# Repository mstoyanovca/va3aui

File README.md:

Direct RF sampling HF SDR transceiver

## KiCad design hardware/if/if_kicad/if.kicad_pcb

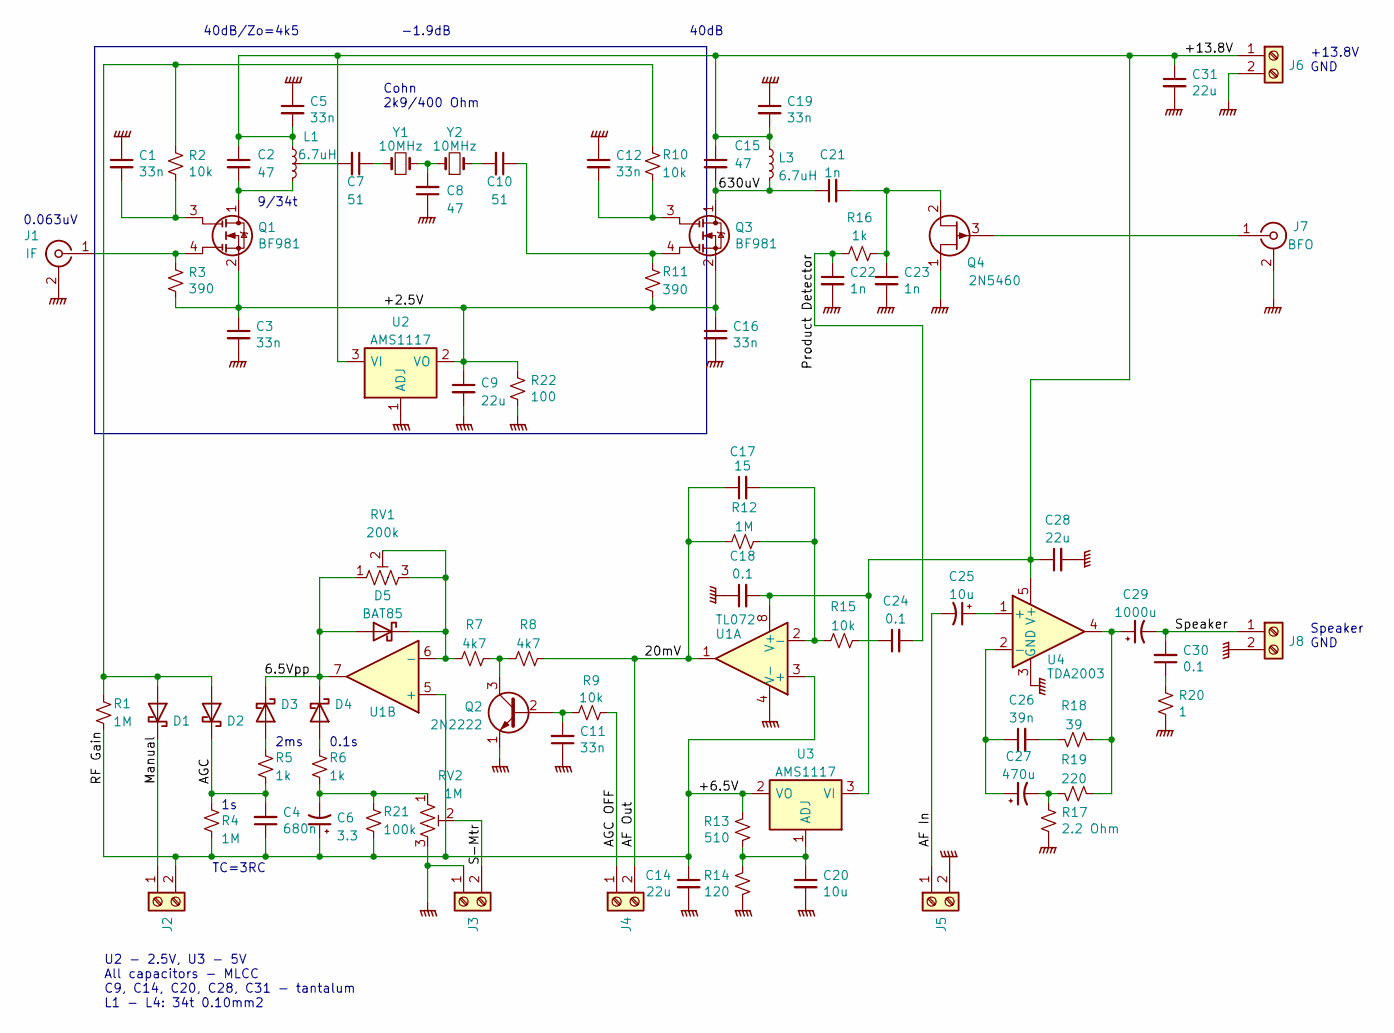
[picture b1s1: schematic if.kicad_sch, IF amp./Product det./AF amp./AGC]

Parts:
C1, C3, C5, C11, C12, C16, C19: 33n; C_Disc_D5.1mm_W3.2mm_P5.00mm_MLCC
C2, C8, C15: 47; C_Disc_D5.1mm_W3.2mm_P5.00mm_MLCC
C4: 680n; C_Disc_D5.1mm_W3.2mm_P5.00mm_MLCC
C6: 3.3; CP_Radial_D4.0mm_H5.0mm_P1.50mm
C7, C10: 51; C_Disc_D5.1mm_W3.2mm_P5.00mm_MLCC
C9, C14, C28, C31: 22u; CP_Radial_Tantal_D5.5mm_P5.00mm
C17: 15; C_Disc_D5.1mm_W3.2mm_P5.00mm_MLCC
C18, C24, C30: 0.1; C_Disc_D5.1mm_W3.2mm_P5.00mm_MLCC
C20: 10u; C_Disc_D5.1mm_W3.2mm_P5.00mm_MLCC
C21, C22, C23: 1n; C_Disc_D5.1mm_W3.2mm_P5.00mm_MLCC
C25: 10u; CP_Radial_D4.0mm_H5.0mm_P2.50mm
C26: 39n; C_Disc_D5.1mm_W3.2mm_P5.00mm_MLCC
C27: 470u; CP_Radial_D6.3mm_H5.0mm_P2.50mm
C29: 1000u; CP_Radial_D8.0mm_H11.5mm_P3.50mm
D1, D2, D3, D4, D5: BAT85; D_DO-35_SOD27_P7.62mm_Horizontal
J1: IF; SMA
J2, J3, J4, J5, J6, J8: Screw_Terminal_01x02; 2poles_screw_tb
J7: BFO; SMA
L1: 6.7uH; Filter_IF_tap
L3: 6.7uH; Filter_IF
Q1, Q3: BF981
Q2: 2N2222; TO-92_2N2222
Q4: 2N5460; TO-92_2N5460
R1, R4, R12: 1M; R_Axial_DIN0207_L6.3mm_D2.5mm_P10.16mm_Horizontal
R2, R9, R10, R15: 10k; R_Axial_DIN0207_L6.3mm_D2.5mm_P10.16mm_Horizontal
R3, R11: 390; R_Axial_DIN0207_L6.3mm_D2.5mm_P10.16mm_Horizontal
R5, R6, R16: 1k; R_Axial_DIN0207_L6.3mm_D2.5mm_P10.16mm_Horizontal
R7, R8: 4k7; R_Axial_DIN0207_L6.3mm_D2.5mm_P10.16mm_Horizontal
R13: 510; R_Axial_DIN0207_L6.3mm_D2.5mm_P10.16mm_Horizontal
R14: 120; R_Axial_DIN0207_L6.3mm_D2.5mm_P10.16mm_Horizontal
R17: 2.2 Ohm; R_Axial_DIN0207_L6.3mm_D2.5mm_P10.16mm_Horizontal
R18: 39; R_Axial_DIN0207_L6.3mm_D2.5mm_P10.16mm_Horizontal
R19: 220; R_Axial_DIN0207_L6.3mm_D2.5mm_P10.16mm_Horizontal
R20: 1; R_Axial_DIN0207_L6.3mm_D2.5mm_P10.16mm_Horizontal
R21: 100k; R_Axial_DIN0207_L6.3mm_D2.5mm_P10.16mm_Horizontal
R22: 100; R_Axial_DIN0207_L6.3mm_D2.5mm_P10.16mm_Horizontal
RV1: 200k; R_trimmer
RV2: 1M; R_trimmer
U1: TL072
U2, U3: AMS1117
U4: TDA2003; TDA2203
Y1, Y2: 10MHz; HC49-U

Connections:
/6.5Vpp: D3.1 (K), D4.1 (K), D5.2 (A), RV1.1, U1.7
/20mV: C17.1, J4.2, R8.2, R12.1, U1.1
/630uV: C15.2, C21.1, L3.2, L3.5, Q3.1 (D)
/+2.5V: C3.1, C9.1, C16.1, Q1.2 (S), Q3.2 (S), R3.2, R11.2, R22.1, U2.2 (VO); also elsewhere on the board
/+6.5V: C4.1, C6.1, C14.1, J2.2, R1.2, R4.2, R13.1, R21.2, U1.3 (+), U1.5 (+), U3.2 (VO)
/+13.8V: C2.1, C5.2, C15.1, C18.2, C19.2, C28.1, C31.1, J6.1, L1.1, L3.1, L3.3, U1.8 (V+), U2.3 (VI), U3.3 (VI), U4.5 (V+)
/AF In: C25.2, J5.1
/AGC: C4.2, D2.1 (K), R4.1, R5.2
/AGC OFF: J4.1, R9.2
/Manual: D1.1 (K), J2.1
/Product Detector: C22.1, C24.2, R16.1
/Speaker: C29.2, C30.2, J8.1
GNDPWR: C1.1, C3.2, C5.1, C8.1, C9.2, C11.1, C12.1, C14.2, C16.2, C18.1, C19.1, C20.2, C22.2, C23.2, C28.2, C31.2, J1.2 (Ext), J3.1, J5.2, J6.2, J7.2 (Ext), J8.2, L1.6, L1.7, L3.6, L3.7, Q2.1 (E), Q4.1 (S), R14.2, R17.2, R20.2, R22.2, RV2.3, U1.4 (V-), U2.1 (ADJ), U4.3 (GND); also elsewhere on the board
unnamed: C1.2, Q1.3 (G1), R2.2
unnamed: C2.2, L1.2, Q1.1 (D)
unnamed: C6.2, R6.2, R21.1, RV2.1
unnamed: C7.1, Y1.1
unnamed: C7.2, L1.3
unnamed: C8.2, Y1.2, Y2.1
unnamed: C10.2, Y2.2
unnamed: C11.2, Q2.2 (B), R9.1
unnamed: C12.2, Q3.3 (G1), R10.2
unnamed: C17.2, R12.2, R15.1, U1.2 (-)
unnamed: C20.1, R13.2, R14.1, U3.1 (ADJ)
unnamed: C21.2, C23.1, Q4.2 (D), R16.2
unnamed: C24.1, R15.2
unnamed: C25.1, U4.1 (+)
unnamed: C26.1, C27.1, U4.2 (-)
unnamed: C26.2, R18.2
unnamed: C27.2, R17.1, R19.2
unnamed: C29.1, R18.1, R19.1, U4.4
unnamed: C30.1, R20.1
unnamed: D1.2 (A), D2.2 (A), R1.1, R2.1, R10.1
unnamed: D3.2 (A), R5.1
unnamed: D4.2 (A), R6.1
unnamed: D5.1 (K), R7.1, RV1.2, RV1.3, U1.6 (-)
unnamed: J1.1 (In), Q1.4 (G2), R3.1
unnamed: J3.2, RV2.2
unnamed: J7.1 (In), Q4.3 (G)
unnamed: Q2.3 (C), R7.2, R8.1

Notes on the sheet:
TC=3RC
Cohn 2k9/400 Ohm
Speaker GND
0.063uV
40dB/Zo=4k5
0.1s
U2 - 2.5V, U3 - 5V All capacitors - MLCC C9, C14, C20, C28, C31 - tantalum L1 - L4: 34t 0.10mm2
2ms
9/34t
-1.9dB
40dB
+13.8V GND

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
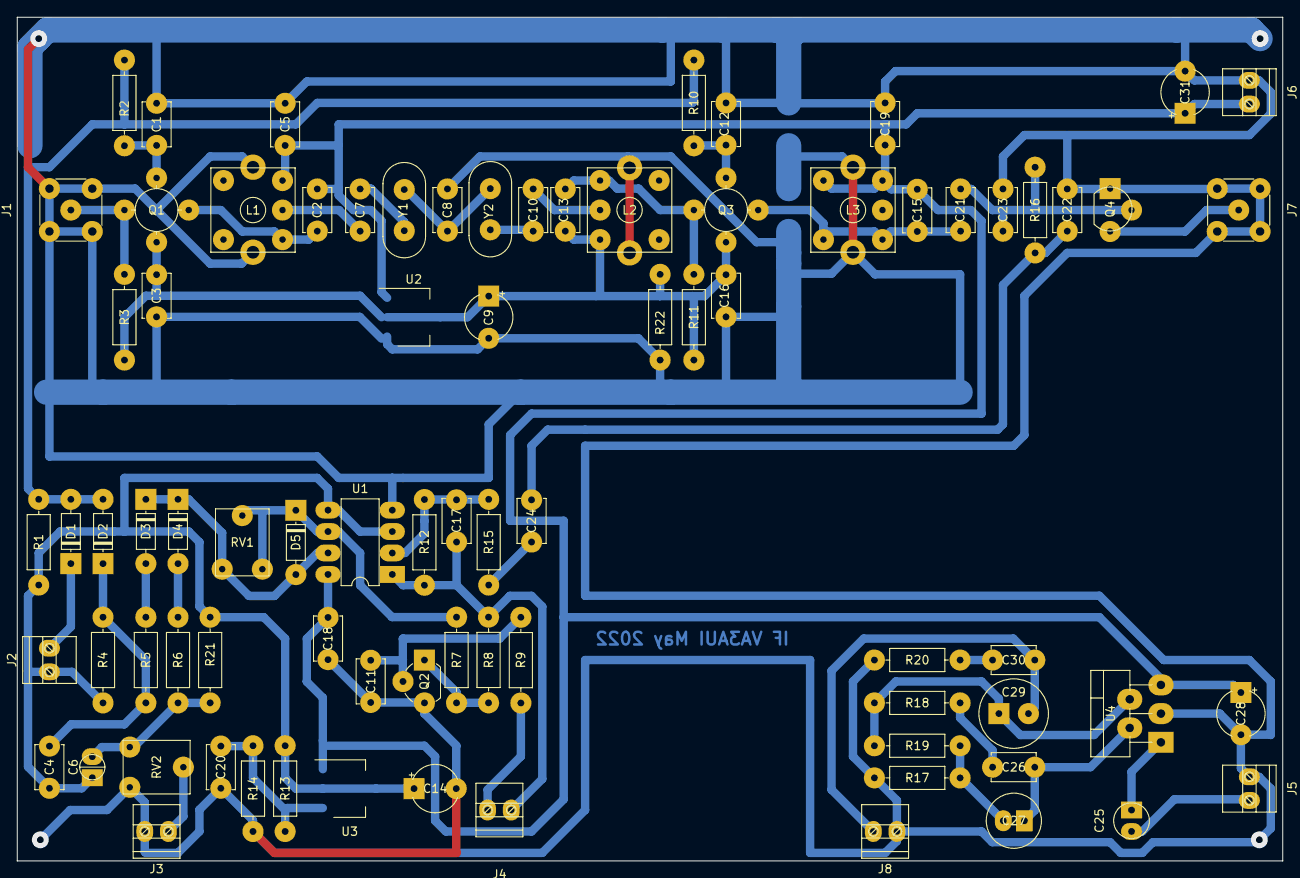
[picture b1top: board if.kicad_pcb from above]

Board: 2 copper layers, 150.0 x 100.0 mm, 81 parts (0 on the bottom side), 42 nets.

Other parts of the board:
C13: 47; C_Disc_D5.1mm_W3.2mm_P5.00mm_MLCC
L2: 6.7uH; Filter_IF_tap

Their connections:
/+2.5V: C13.2, L2.1; also elsewhere on the board
GNDPWR: L2.6, L2.7; also elsewhere on the board

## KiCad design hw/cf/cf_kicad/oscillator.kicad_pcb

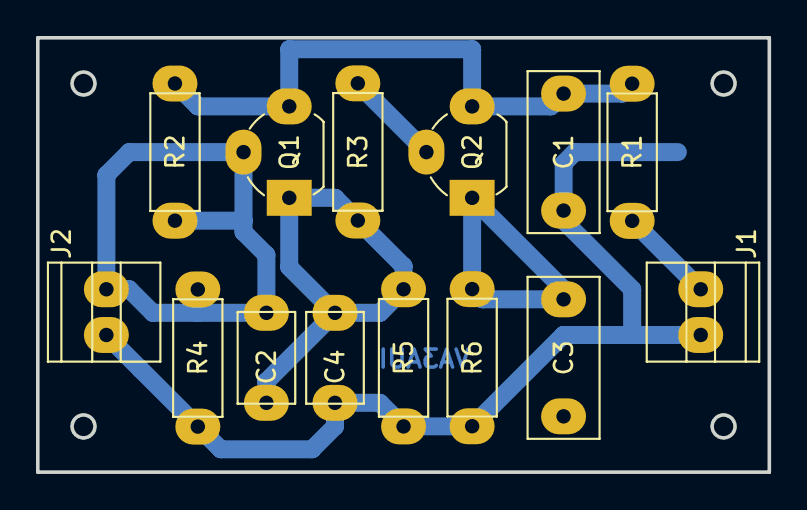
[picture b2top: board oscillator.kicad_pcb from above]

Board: 2 copper layers, 40.6 x 24.1 mm, 14 parts (0 on the bottom side), 7 nets.

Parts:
C1, C3: 0.1; C_Disc_D9.0mm_W4.0mm_P6.50mm_100n
C2: 150; C_Disc_D5.1mm_W3.2mm_P5.00mm_MLCC
C4: 330; C_Disc_D5.1mm_W3.2mm_P5.00mm_MLCC
J1: +13.8V; 2poles_screw_tb
J2: Crystal 3MHz; 2poles_screw_tb
Q1, Q2: 2N3904; TO-92_2N3904
R1: 47; R_Axial_L6.3mm_D2.5mm_P7.62mm_0.25W
R2, R4: 10k; R_Axial_L6.3mm_D2.5mm_P7.62mm_0.25W
R3, R5, R6: 1k; R_Axial_L6.3mm_D2.5mm_P7.62mm_0.25W

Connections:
GNDPWR: C1.1, C4.2, J1.1, J2.2, R4.2, R5.2, R6.1
unnamed: J1.2, R1.2
unnamed: C2.1, J2.1, Q1.2 (B), R2.2, R4.1
unnamed: C1.2, Q1.3 (C), Q2.3 (C), R1.1, R2.1
unnamed: C2.2, C4.1, Q1.1 (E), R3.1, R5.1
unnamed: Q2.2 (B), R3.2
unnamed: C3.1, Q2.1 (E), R6.2

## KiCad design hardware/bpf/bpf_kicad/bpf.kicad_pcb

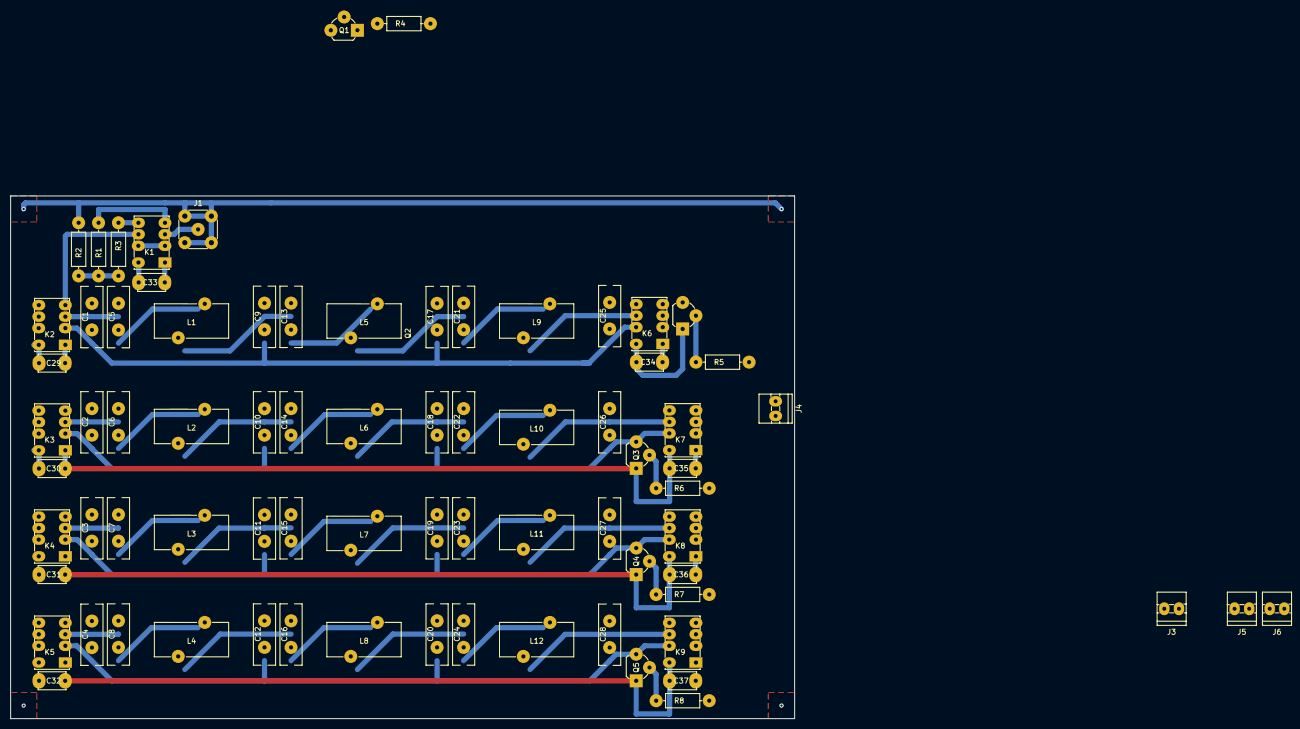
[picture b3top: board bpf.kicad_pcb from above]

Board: 2 copper layers, 150.0 x 100.0 mm, 76 parts (0 on the bottom side), 50 nets.

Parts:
C1, C3: 120; C_Rect_L11.5mm_W4.0mm_P5.00mm_Silver_Mica
C2: 135*; C_Rect_L11.5mm_W4.0mm_P5.00mm_Silver_Mica
C4, C7: 160; C_Rect_L11.5mm_W4.0mm_P5.00mm_Silver_Mica
C5, C6: 620; C_Rect_L11.5mm_W4.0mm_P5.00mm_Silver_Mica
C8, C10: 36; C_Rect_L11.5mm_W4.0mm_P5.00mm_Silver_Mica
C9, C15, C17: 39; C_Rect_L11.5mm_W4.0mm_P5.00mm_Silver_Mica
C11, C14: 91; C_Rect_L11.5mm_W4.0mm_P5.00mm_Silver_Mica
C12, C13: 270; C_Rect_L11.5mm_W4.0mm_P5.00mm_Silver_Mica
C16: 41*; C_Rect_L11.5mm_W4.0mm_P5.00mm_Silver_Mica
C18, C21: 110; C_Rect_L11.5mm_W4.0mm_P5.00mm_Silver_Mica
C19, C20: 240; C_Rect_L11.5mm_W4.0mm_P5.00mm_Silver_Mica
C22, C24: 30; C_Rect_L11.5mm_W4.0mm_P5.00mm_Silver_Mica
C23: 33; C_Rect_L11.5mm_W4.0mm_P5.00mm_Silver_Mica
C25, C28: 82; C_Rect_L11.5mm_W4.0mm_P5.00mm_Silver_Mica
C26, C27: 180; C_Rect_L11.5mm_W4.0mm_P5.00mm_Silver_Mica
C29, C30, C31, C32, C33, C34, C35, C36, C37: 33n; C_Disc_D5.1mm_W3.2mm_P5.00mm_MLCC
J1: Conn_Coaxial; SMA
J3, J4, J5, J6: Screw_Terminal_01x02; 2poles_screw_tb
K1, K2, K3, K4, K5, K6, K7, K8, K9: G6K; G6K-2P-Y
L1, L2, L3: 5.23uH; T50-6
L4, L5, L6: 3.83uH; T50-6
L7, L8, L9: 1.78uH; T50-6
L10, L11, L12: 1.24uH; T50-6
Q1, Q2, Q3, Q4, Q5: 2N2222; TO-92_2N2222
R1, R2: 30; R_Axial_DIN0207_L6.3mm_D2.5mm_P10.16mm_Horizontal
R3: 1M; R_Axial_DIN0207_L6.3mm_D2.5mm_P10.16mm_Horizontal
R4: 27; R_Axial_DIN0207_L6.3mm_D2.5mm_P10.16mm_Horizontal
R5, R6, R7, R8: 10k; R_Axial_DIN0207_L6.3mm_D2.5mm_P10.16mm_Horizontal

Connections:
+5V: K3.5, K5.5, K7.5, K9.5
/10m: C36.2, C37.2, K8.1, K9.8, Q5.3 (C)
/15m: C34.2, C35.2, K6.1, K7.8, Q4.3 (C)
/20m: C32.2, C33.2, K4.1, K5.8, Q3.3 (C)
/40m: C30.2, C31.2, K2.1, K3.8, Q2.3 (C)
/+13.8V: C29.1, C30.1, C31.1, C32.1, C33.1, C34.1, C35.1, C36.1, C37.1, J3.2, K1.1, K2.8, K3.1, K4.8, K5.1, K6.8, K7.1, K8.8, K9.1
/Ant: J1.1 (In), K1.3, R3.2
/Att: C29.2, K1.8, Q1.3 (C)
/Att -12dB: K1.2, K1.7
/BPF: K1.6, K2.4, K4.4, K6.4, K8.4
GNDPWR: C4.1, C5.1, C6.1, C7.1, C11.1, C12.1, C13.1, C14.1, C18.1, C19.1, C20.1, C21.1, C25.1, C26.1, C27.1, C28.1, J1.2 (Ext), J6.1, J6.2, K2.2, K3.7, K4.2, K5.7, K6.2, K7.7, K8.2, K9.7, Q1.1 (E), Q2.1 (E), Q3.1 (E), Q4.1 (E), Q5.1 (E), R3.1, R4.1
unnamed: C1.1, L1.1
unnamed: C1.2, C4.2, K2.3
unnamed: C2.1, L2.1
unnamed: C2.2, C5.2, L1.2
unnamed: C3.1, L3.1
unnamed: C3.2, C6.2, L2.2
unnamed: C7.2, K3.6, L3.2
unnamed: C8.1, L4.1
unnamed: C9.1, L5.1
unnamed: C10.1, L6.1
unnamed: C10.2, C13.2, L5.2
unnamed: C8.2, C11.2, K4.3
unnamed: C9.2, C12.2, L4.2
unnamed: C14.2, K5.6, L6.2
unnamed: C15.1, L7.1
unnamed: C15.2, C18.2, K6.3
unnamed: C16.1, L8.1
unnamed: C16.2, C19.2, L7.2
unnamed: C17.1, L9.1
unnamed: C17.2, C20.2, L8.2
unnamed: C21.2, K7.6, L9.2
unnamed: C22.1, L10.1
unnamed: C22.2, C25.2, K8.3
unnamed: C23.1, L11.1
unnamed: C23.2, C26.2, L10.2
unnamed: C24.1, L12.1
unnamed: C24.2, C27.2, L11.2
unnamed: C28.2, K9.6, L12.2
unnamed: J3.1, R5.1
unnamed: J4.1, R7.1
unnamed: J4.2, R6.1
unnamed: J5.2, R8.1
unnamed: K1.4, R1.1
unnamed: K1.5, R2.2
unnamed: Q1.2 (B), R5.2
unnamed: Q2.2 (B), R6.2
unnamed: Q3.2 (B), R7.2
unnamed: Q4.2 (B), R8.2
unnamed: R1.2, R2.1, R4.2

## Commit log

2024-10-29 added README
2024-11-01 added HW files
2024-11-02 added rx.m
2024-11-05 added iq demodulator
2024-11-05 deletion unused
2024-11-06 completed iq_demodulator
2024-11-22 added sdr vhdl
2024-11-24 added hw folder
2024-12-07 switched to Gowin
2024-12-09 created dds
2024-12-11 modified dds
2024-12-16 created rx
2024-12-23 switched to tang nano 20k
2024-12-23 cleaning
2025-01-07 added ZYNQ 7000 files
2025-01-14 4bit counter
2025-01-26 added tb file
2025-01-29 deleted 4-bit counter
2025-01-29 modified .gitignore
2025-01-31 generated a sine ouput
2025-02-01 created a sine output
2025-02-02 working on DDS
2025-02-06 completed dds
